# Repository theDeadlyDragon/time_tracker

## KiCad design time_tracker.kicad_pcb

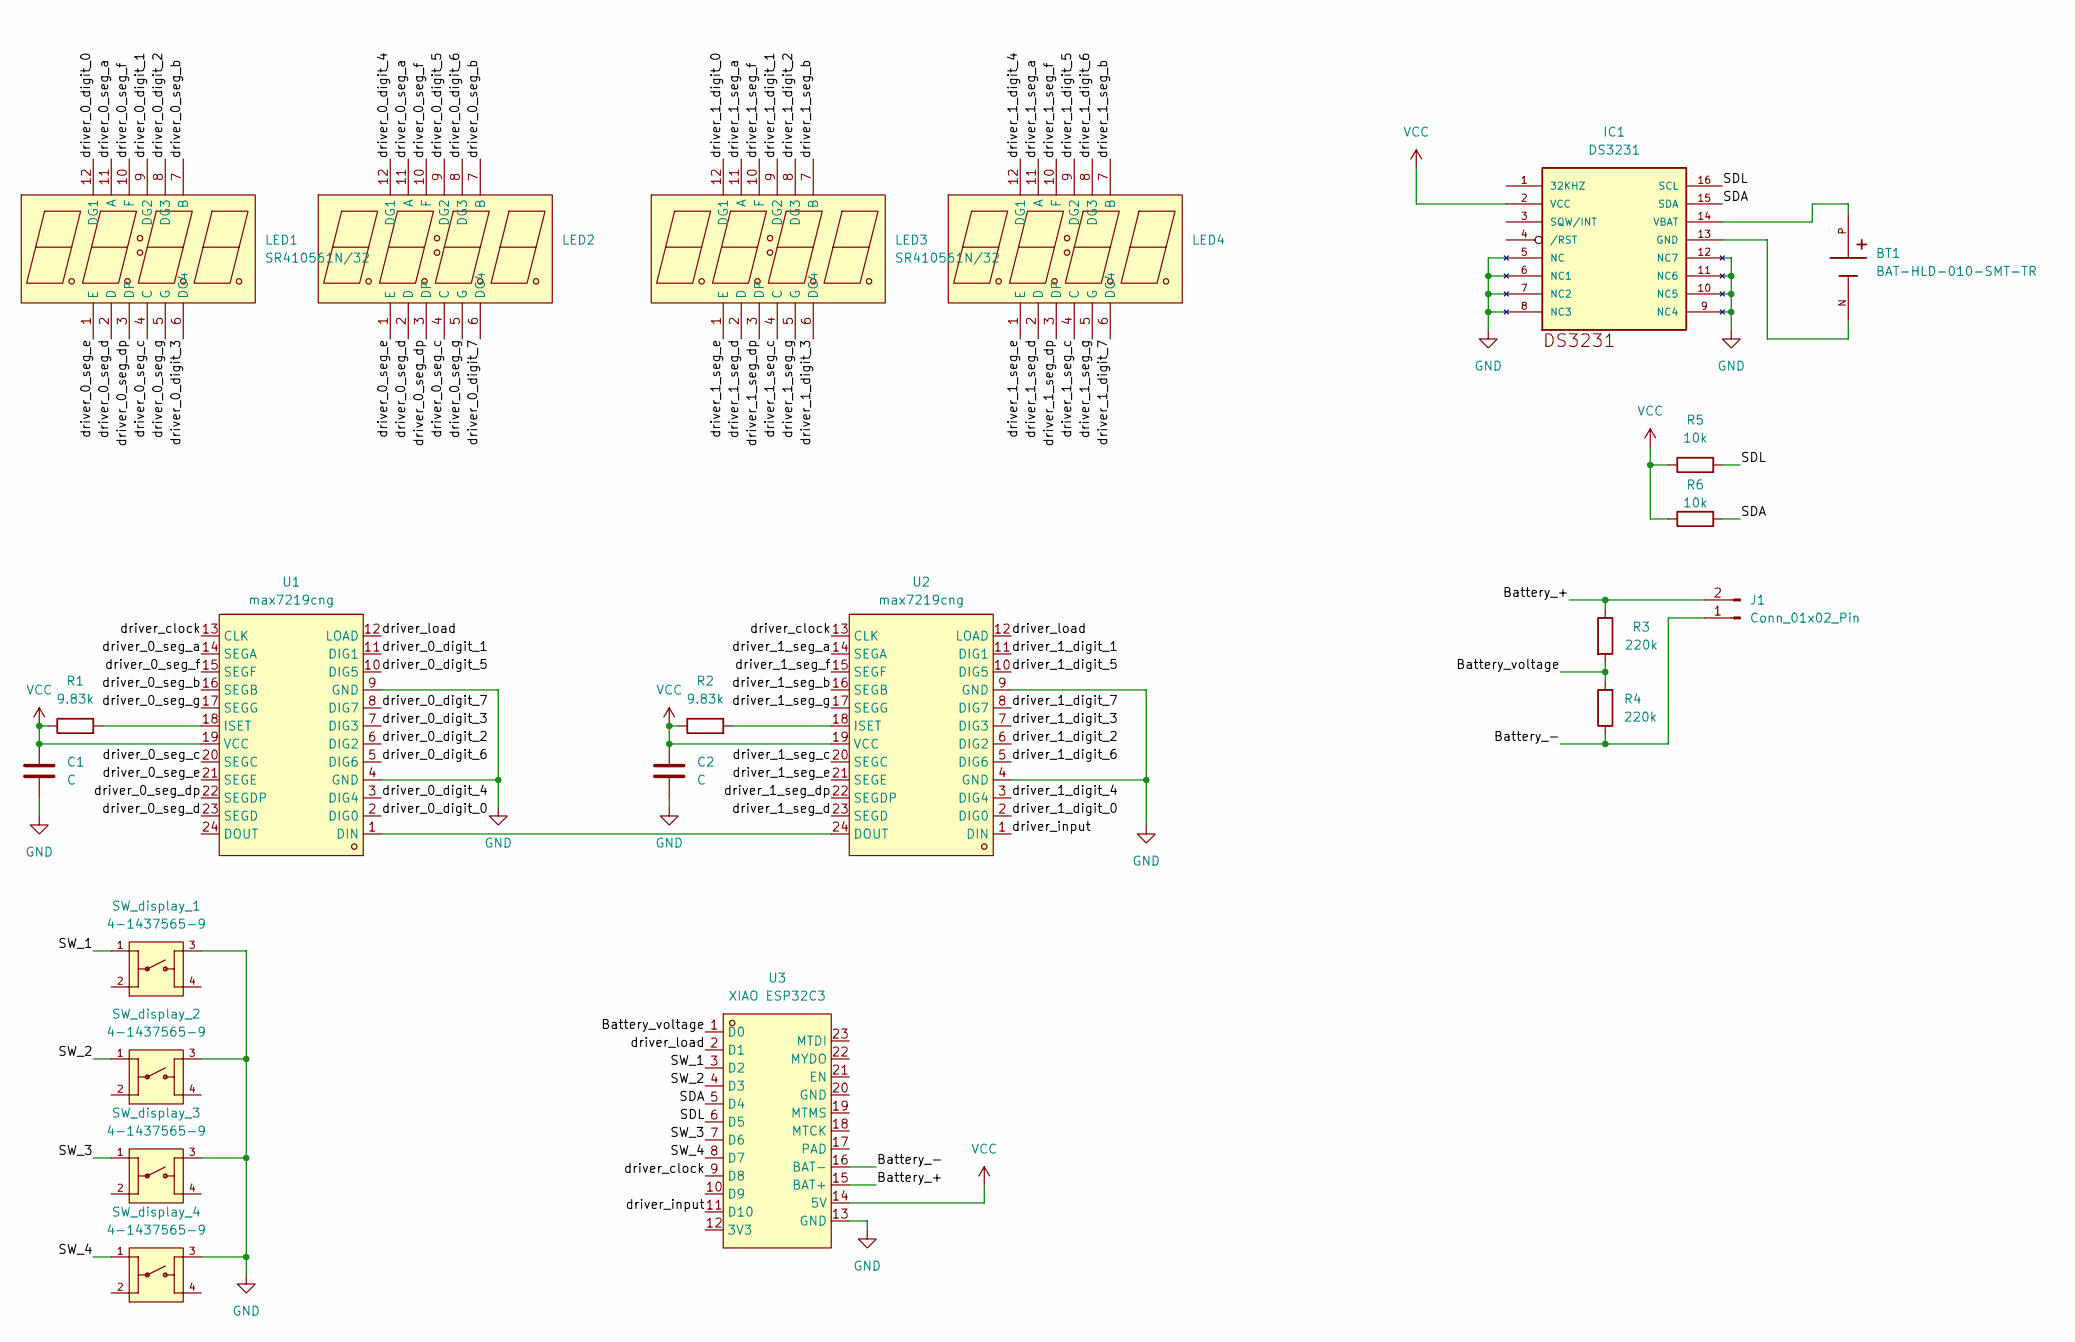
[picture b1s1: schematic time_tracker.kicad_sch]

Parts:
BT1: BAT-HLD-010-SMT-TR; BAT_BAT-HLD-010-SMT-TR
C1, C2: C; C_0504_1310Metric_Pad0.83x1.28mm_HandSolder
IC1: DS3231; SO16W
J1: Conn_01x02_Pin; PinHeader_1x02_P2.54mm_Vertical
LED1, LED2, LED3, LED4: SR410561N/32; SR410561N; LCSC Part C33545970
R1, R2: 9.83k; R_1206_3216Metric
R3, R4: 220k; R_1206_3216Metric
R5, R6: 10k; R_1206_3216Metric
SW_display_1, SW_display_2, SW_display_3, SW_display_4: 4-1437565-9; TE_4-1437565-9; PARTREV V
U1, U2: max7219cng; MAX7219; LCSC Part C29160
U3: XIAO ESP32C3; MCU_Seeed_ESP32C3; LCSC Part C19189385

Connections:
/Battery_+: J1.2, R3.1, U3.15 (BAT+)
/Battery_-: J1.1, R4.1, U3.16 (BAT-)
/Battery_voltage: R3.2, R4.2, U3.1 (D0)
/SDA: IC1.15 (SDA), R6.2, U3.5 (D4)
/SDL: IC1.16 (SCL), R5.2, U3.6 (D5)
/SW_1: SW_display_1.1, U3.3 (D2)
/SW_2: SW_display_2.1, U3.4 (D3)
/SW_3: SW_display_3.1, U3.7 (D6)
/SW_4: SW_display_4.1, U3.8 (D7)
/driver_0_digit_0: LED1.12 (DG1), U1.2 (DIG0)
/driver_0_digit_1: LED1.9 (DG2), U1.11 (DIG1)
/driver_0_digit_2: LED1.8 (DG3), U1.6 (DIG2)
/driver_0_digit_3: LED1.6 (DG4), U1.7 (DIG3)
/driver_0_digit_4: LED2.12 (DG1), U1.3 (DIG4)
/driver_0_digit_5: LED2.9 (DG2), U1.10 (DIG5)
/driver_0_digit_6: LED2.8 (DG3), U1.5 (DIG6)
/driver_0_digit_7: LED2.6 (DG4), U1.8 (DIG7)
/driver_0_seg_a: LED1.11 (A), LED2.11 (A), U1.14 (SEGA)
/driver_0_seg_b: LED1.7 (B), LED2.7 (B), U1.16 (SEGB)
/driver_0_seg_c: LED1.4 (C), LED2.4 (C), U1.20 (SEGC)
/driver_0_seg_d: LED1.2 (D), LED2.2 (D), U1.23 (SEGD)
/driver_0_seg_dp: LED1.3 (DP), LED2.3 (DP), U1.22 (SEGDP)
/driver_0_seg_e: LED1.1 (E), LED2.1 (E), U1.21 (SEGE)
/driver_0_seg_f: LED1.10 (F), LED2.10 (F), U1.15 (SEGF)
/driver_0_seg_g: LED1.5 (G), LED2.5 (G), U1.17 (SEGG)
/driver_1_digit_0: LED3.12 (DG1), U2.2 (DIG0)
/driver_1_digit_1: LED3.9 (DG2), U2.11 (DIG1)
/driver_1_digit_2: LED3.8 (DG3), U2.6 (DIG2)
/driver_1_digit_3: LED3.6 (DG4), U2.7 (DIG3)
/driver_1_digit_4: LED4.12 (DG1), U2.3 (DIG4)
/driver_1_digit_5: LED4.9 (DG2), U2.10 (DIG5)
/driver_1_digit_6: LED4.8 (DG3), U2.5 (DIG6)
/driver_1_digit_7: LED4.6 (DG4), U2.8 (DIG7)
/driver_1_seg_a: LED3.11 (A), LED4.11 (A), U2.14 (SEGA)
/driver_1_seg_b: LED3.7 (B), LED4.7 (B), U2.16 (SEGB)
/driver_1_seg_c: LED3.4 (C), LED4.4 (C), U2.20 (SEGC)
/driver_1_seg_d: LED3.2 (D), LED4.2 (D), U2.23 (SEGD)
/driver_1_seg_dp: LED3.3 (DP), LED4.3 (DP), U2.22 (SEGDP)
/driver_1_seg_e: LED3.1 (E), LED4.1 (E), U2.21 (SEGE)
/driver_1_seg_f: LED3.10 (F), LED4.10 (F), U2.15 (SEGF)
/driver_1_seg_g: LED3.5 (G), LED4.5 (G), U2.17 (SEGG)
/driver_clock: U1.13 (CLK), U2.13 (CLK), U3.9 (D8)
/driver_input: U2.1 (DIN), U3.11 (D10)
/driver_load: U1.12 (LOAD), U2.12 (LOAD), U3.2 (D1)
GND: C1.2, C2.2, IC1.5 (NC), IC1.6 (NC1), IC1.7 (NC2), IC1.8 (NC3), IC1.9 (NC4), IC1.10 (NC5), IC1.11 (NC6), IC1.12 (NC7), SW_display_1.3, SW_display_2.3, SW_display_3.3, SW_display_4.3, U1.4 (GND), U1.9 (GND), U2.4 (GND), U2.9 (GND), U3.13 (GND)
unnamed: BT1.N, IC1.13 (GND)
unnamed: BT1.P, IC1.14 (VBAT)
unnamed: U1.1 (DIN), U2.24 (DOUT)
unnamed: R1.2, U1.18 (ISET)
unnamed: R2.2, U2.18 (ISET)
VCC: C1.1, C2.1, IC1.2 (VCC), R1.1, R2.1, R5.1, R6.1, U1.19 (VCC), U2.19 (VCC), U3.14 (5V)

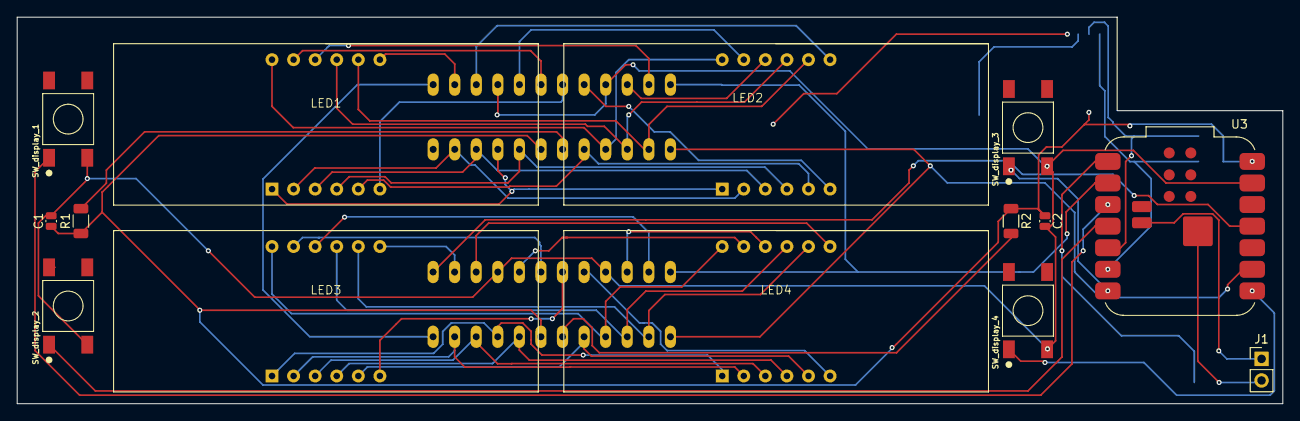
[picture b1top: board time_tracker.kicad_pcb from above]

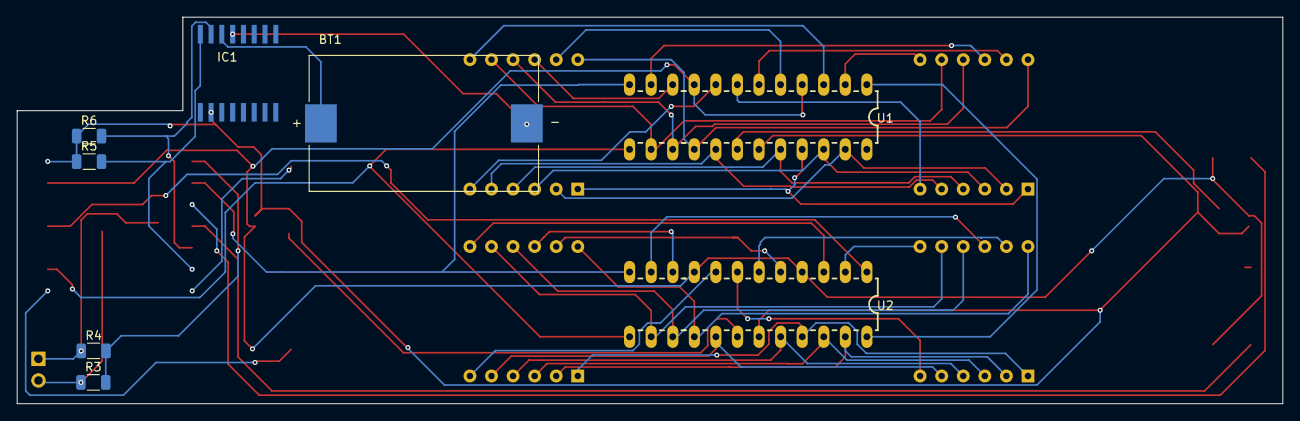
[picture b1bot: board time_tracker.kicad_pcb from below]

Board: 2 copper layers, 149.0 x 45.5 mm, 22 parts (8 on the bottom side), 51 nets.

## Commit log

2026-01-31 Init
2026-02-01 added rtc, battery circuit
2026-02-01 added rtc
